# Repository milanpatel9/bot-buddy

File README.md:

# BotBuddy

BotBuddy is a remote-controlled tank platform developed to explore embedded systems, motor control, and wireless communication. Built from the ground up in 2023, this project integrates real-time control, sensor feedback, and a mobile input interface to create a responsive robotics experience.

## Features

- 🎮 **Remote Control**: Receives movement commands via Bluetooth from a custom mobile controller interface.
- ⚙️ **Motor Control**: Dual motor setup for differential steering using PWM signals.
- 🔋 **Battery Powered**: Runs on an onboard power supply for wireless mobility.
- 🧭 **Sensor Integration (optional)**: Designed to support distance sensing and obstacle avoidance (planned for expansion).

## Technical Stack

- **Microcontroller**: Arduino UNO (or ESP32 if applicable)
- **Control Interface**: Bluetooth module (e.g., HC-05 or BLE)
- **Programming Language**: C++ (Arduino Framework)
- **Motors**: DC motors with L298N motor driver
- **Chassis**: Custom or kit-based tracked tank platform

## Project Goals

- Learn real-time embedded control and motor driving principles
- Implement reliable Bluetooth communication for remote operation
- Design a functional robotic base for future autonomous features

## Future Enhancements

- Add ultrasonic sensors for object detection and avoidance
- Incorporate a camera module for FPV streaming
- Upgrade to Wi-Fi-based remote control and web dashboard

---

Created as a 2023 personal robotics project to gain hands-on experience with embedded hardware, robotics design, and mobile interfacing.

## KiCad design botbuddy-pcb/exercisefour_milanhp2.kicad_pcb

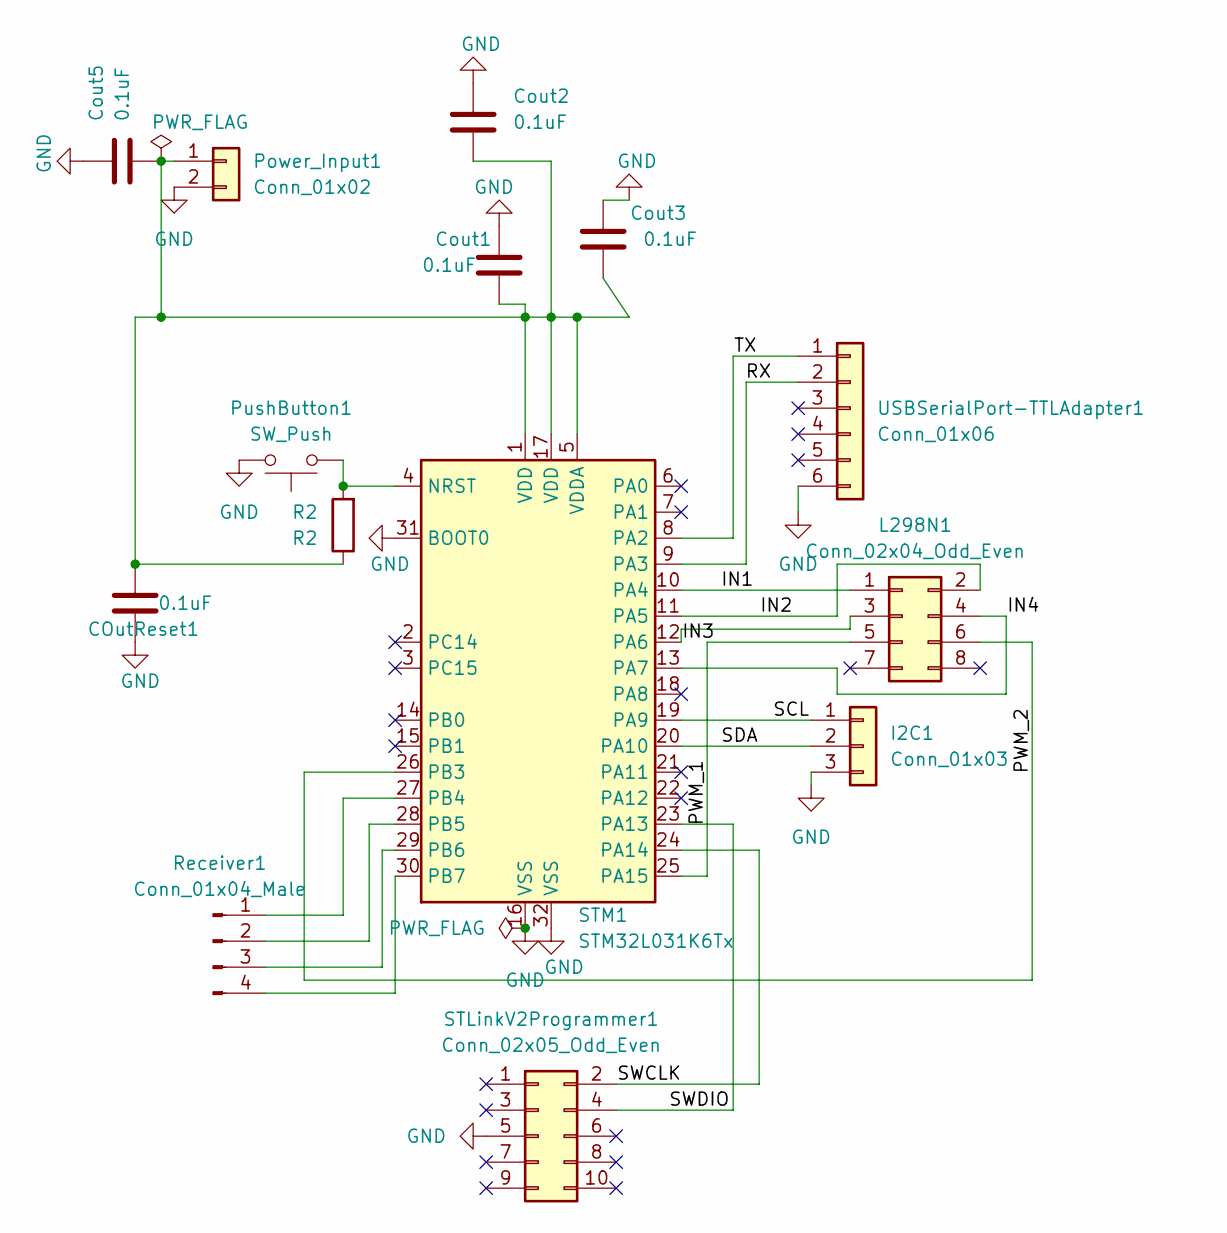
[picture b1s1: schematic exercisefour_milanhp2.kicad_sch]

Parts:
COutReset1: 0.1uF; C_0805_2012Metric_Pad1.18x1.45mm_HandSolder
Cout1, Cout2, Cout3, Cout5: 0.1uF; C_0805_2012Metric_Pad1.18x1.45mm_HandSolder
I2C1: Conn_01x03; PinHeader_1x03_P2.54mm_Vertical
L298N1: Conn_02x04_Odd_Even; PinHeader_2x04_P2.54mm_Vertical
Power_Input1: Conn_01x02; PinHeader_1x02_P2.54mm_Vertical
PushButton1: SW_Push; SW_PUSH_6mm_H4.3mm
R2: R2; R_0805_2012Metric_Pad1.20x1.40mm_HandSolder
Receiver1: Conn_01x04_Male; PinHeader_1x04_P2.54mm_Vertical
STLinkV2Programmer1: Conn_02x05_Odd_Even; PinHeader_2x05_P2.54mm_Vertical
STM1: STM32L031K6Tx; LQFP-32_7x7mm_P0.8mm
USBSerialPort-TTLAdapter1: Conn_01x06; PinHeader_1x06_P2.54mm_Vertical

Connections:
/IN1: L298N1.1, STM1.10 (PA4)
/IN2: L298N1.2, STM1.11 (PA5)
/IN3: L298N1.3, STM1.12 (PA6)
/IN4: L298N1.4, STM1.13 (PA7)
/PWM_1: L298N1.5, STM1.25 (PA15)
/PWM_2: L298N1.6, STM1.26 (PB3)
/RX: STM1.9 (PA3), USBSerialPort-TTLAdapter1.2
/SCL: I2C1.1, STM1.19 (PA9)
/SDA: I2C1.2, STM1.20 (PA10)
/SWCLK: STLinkV2Programmer1.2, STM1.24 (PA14)
/SWDIO: STLinkV2Programmer1.4, STM1.23 (PA13)
/TX: STM1.8 (PA2), USBSerialPort-TTLAdapter1.1
GND: COutReset1.1, Cout1.1, Cout2.1, Cout3.1, Cout5.1, I2C1.3, Power_Input1.2, PushButton1.2, STLinkV2Programmer1.5, STM1.16 (VSS), STM1.31 (BOOT0), STM1.32 (VSS), USBSerialPort-TTLAdapter1.6
unnamed: COutReset1.2, Cout1.2, Cout2.2, Cout3.2, Cout5.2, Power_Input1.1, R2.1, STM1.1 (VDD), STM1.5 (VDDA), STM1.17 (VDD)
unnamed: PushButton1.1, R2.2, STM1.4 (NRST)
unnamed: Receiver1.1, STM1.27 (PB4)
unnamed: Receiver1.2, STM1.28 (PB5)
unnamed: Receiver1.3, STM1.29 (PB6)
unnamed: Receiver1.4, STM1.30 (PB7)

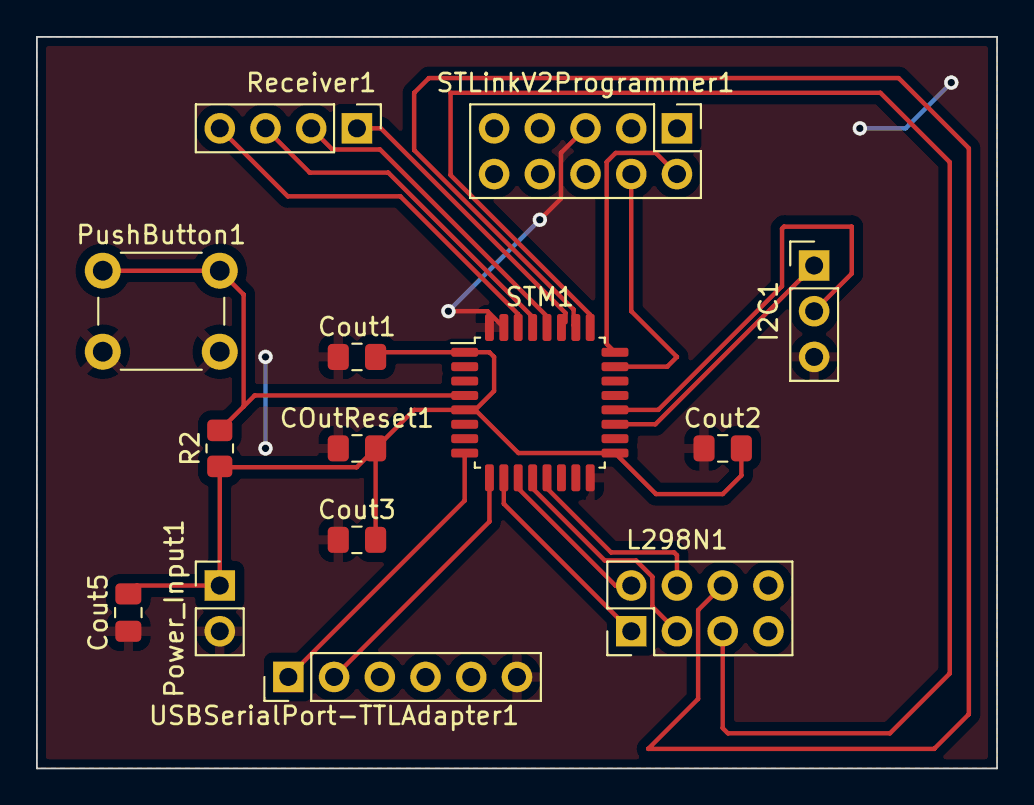
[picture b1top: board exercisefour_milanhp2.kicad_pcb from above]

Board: 2 copper layers, 53.3 x 40.6 mm, 14 parts (0 on the bottom side), 19 nets.

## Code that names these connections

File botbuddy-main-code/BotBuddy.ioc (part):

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Mcu.Name=STM32L031K(4-6)Tx
Mcu.Package=LQFP32
Mcu.UserName=STM32L031K6Tx
PA10.Signal=GPIO_Output
PA15.Signal=S_TIM2_CH1
PA2.Mode=Asynchronous
PA2.Signal=LPUART1_TX
PA3.Mode=Asynchronous
PA3.Signal=LPUART1_RX
PA4.GPIOParameters=GPIO_Speed,PinState
PA4.GPIO_Speed=GPIO_SPEED_FREQ_LOW
PA4.PinState=GPIO_PIN_RESET
PA4.Signal=GPIO_Output
PA5.GPIOParameters=GPIO_Speed,PinState
PA5.GPIO_Speed=GPIO_SPEED_FREQ_LOW
PA5.PinState=GPIO_PIN_RESET
PA5.Signal=GPIO_Output
PA6.GPIOParameters=GPIO_Speed,PinState
PA6.GPIO_Speed=GPIO_SPEED_FREQ_LOW
PA6.PinState=GPIO_PIN_RESET
PA6.Signal=GPIO_Output
PA7.GPIOParameters=GPIO_Speed,PinState
PA7.GPIO_Speed=GPIO_SPEED_FREQ_LOW
PA7.PinState=GPIO_PIN_RESET
PA7.Signal=GPIO_Output
PA9.Signal=GPIO_Output
PB3.Signal=S_TIM2_CH2
PB4.Signal=GPIO_Input
PB5.Signal=GPIO_Input
PB6.Signal=GPIO_Input
PB7.Signal=GPIO_Input
RCC.HSE_VALUE=8000000
RCC.SYSCLKFreq_VALUE=2097000
board=custom

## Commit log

2025-06-25 Added all source code, pcb files, and README.md
